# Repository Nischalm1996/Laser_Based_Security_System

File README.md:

# Laser_Based_Security_System

## Pin Connections
| NAME     |PIN|
| ---      | ---|
|LASER|D5|
| LASER1|D6|
| Buzzer|D8|
| LED|D10|
| DETECT|D2|
| DETECT1|D7|
|RX_GSM|D3|
| TX_GSM|D4|

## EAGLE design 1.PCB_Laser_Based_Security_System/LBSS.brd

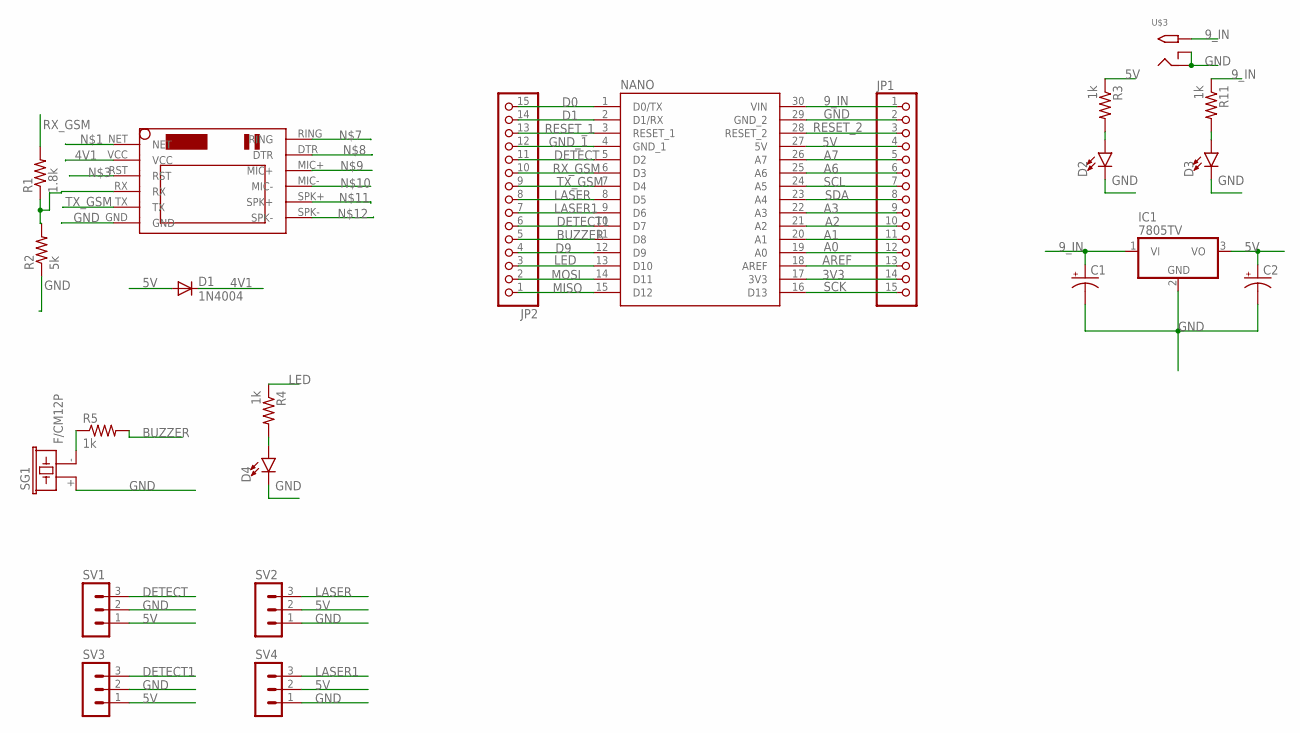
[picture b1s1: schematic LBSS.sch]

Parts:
C1, C2: CPOL-USE3.5-8; E3,5-8
D1: 1N4004; DO41-10
D2, D3, D4: LED3MM; LED_3MM
IC1: 7805TV; TO220V
JP1, JP2: PINHD-1X15; 1X15
NANO: A000005; MODULE_A000005
R1: 1.8k; 0207/10
R2: 5k; 0207/10
R3, R4, R5, R11: 1k; M0805
SG1: F/CM12P
SV1, SV2, SV3, SV4: MA03-1
U$1: SIM800LMODULE
U$3: 2.1MMJACKTHM; PJ-102A

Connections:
3V3: JP1.14, NANO.17 (3V3)
4V1: D1.C, U$1.VCC
5V: C2.+, D1.A, IC1.3 (VO), JP1.4, NANO.27 (5V), R3.1, SV1.1, SV2.2, SV3.1, SV4.2
9_IN: C1.+, IC1.1 (VI), JP1.1, NANO.30 (VIN), R11.1, U$3.TIP
A0: JP1.12, NANO.19 (A0)
A1: JP1.11, NANO.20 (A1)
A2: JP1.10, NANO.21 (A2)
A3: JP1.9, NANO.22 (A3)
A6: JP1.6, NANO.25 (A6)
A7: JP1.5, NANO.26 (A7)
AREF: JP1.13, NANO.18 (AREF)
BUZZER: JP2.5, NANO.11 (D8), R5.2
D0: JP2.15, NANO.1 (D0/TX)
D1: JP2.14, NANO.2 (D1/RX)
D9: JP2.4, NANO.12 (D9)
DETECT: JP2.11, NANO.5 (D2), SV1.3
DETECT1: JP2.6, NANO.10 (D7), SV3.3
GND: C1.-, C2.-, D2.K (C), D3.K (C), D4.K (C), IC1.2 (GND), JP1.2, NANO.29 (GND_2), R2.1, SG1.+ (1), SV1.2, SV2.1, SV3.2, SV4.1, U$1.GND, U$3.RING, U$3.RING_SW
GND_1: JP2.12, NANO.4 (GND_1)
LASER: JP2.8, NANO.8 (D5), SV2.3
LASER1: JP2.7, NANO.9 (D6), SV4.3
LED: JP2.3, NANO.13 (D10), R4.1
MISO: JP2.1, NANO.15 (D12)
MOSI: JP2.2, NANO.14 (D11)
unnamed: D3.A, R11.2
unnamed: R1.1, R2.2, U$1.RX
unnamed: D2.A, R3.2
unnamed: R5.1, SG1.- (2)
unnamed: D4.A, R4.2
RESET_1: JP2.13, NANO.3 (RESET_1)
RESET_2: JP1.3, NANO.28 (RESET_2)
RX_GSM: JP2.10, NANO.6 (D3), R1.2
SCK: JP1.15, NANO.16 (D13)
SCL: JP1.7, NANO.24 (A5)
SDA: JP1.8, NANO.23 (A4)
TX_GSM: JP2.9, NANO.7 (D4), U$1.TX

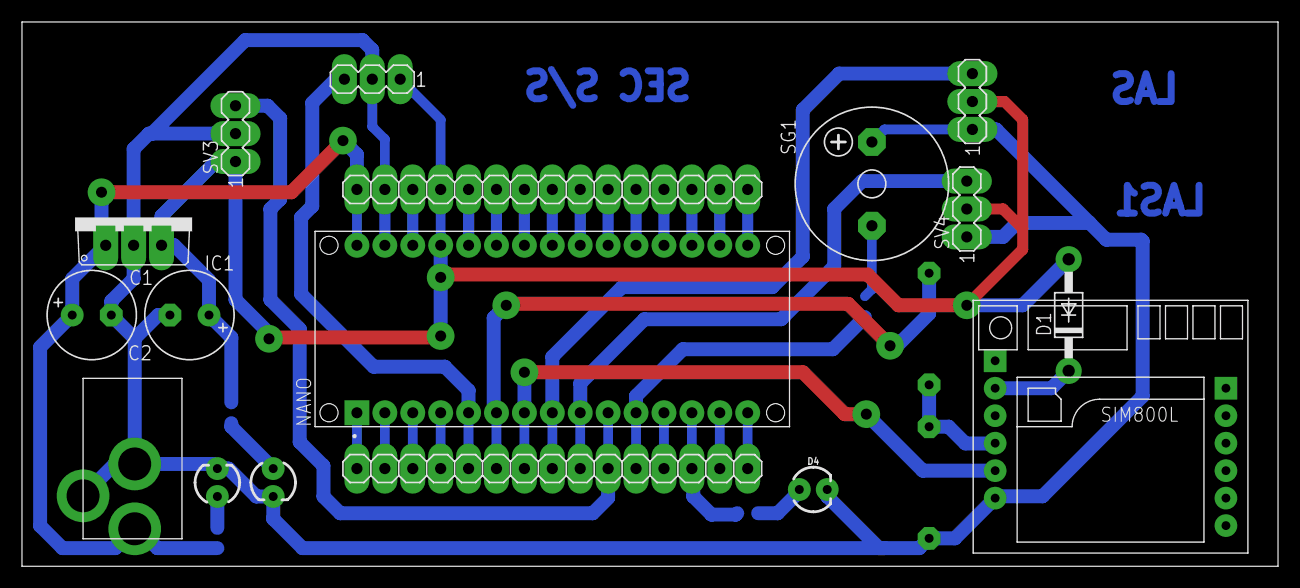
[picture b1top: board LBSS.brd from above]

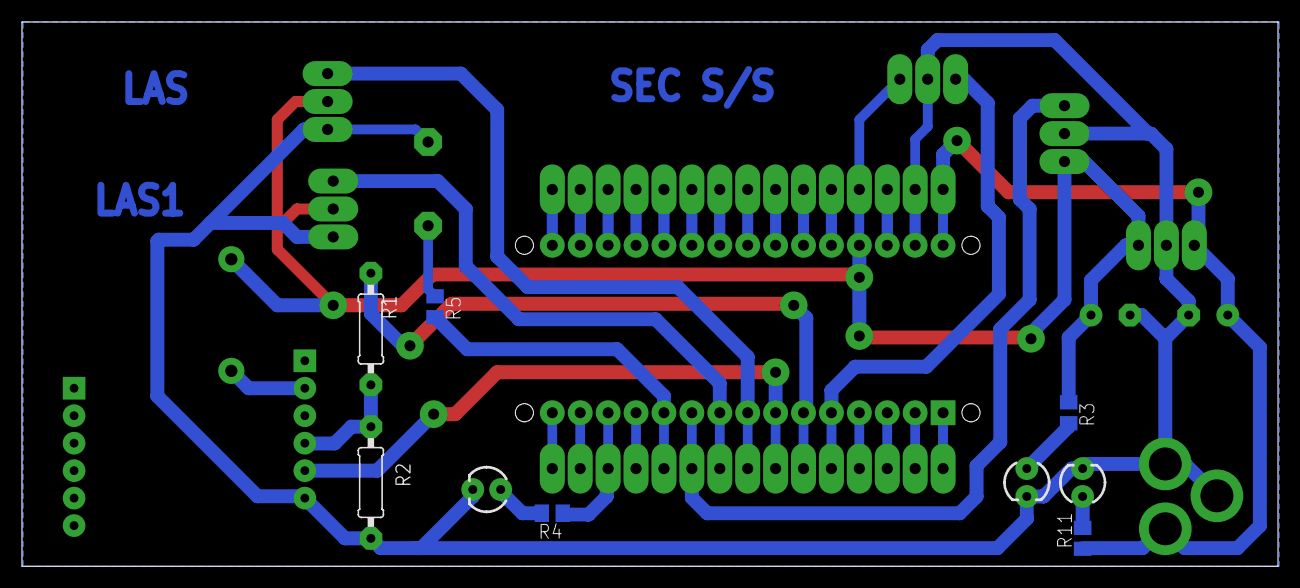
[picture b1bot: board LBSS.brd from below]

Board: 2 copper layers, 114.3 x 49.5 mm, 23 parts (6 on the bottom side), 36 nets.

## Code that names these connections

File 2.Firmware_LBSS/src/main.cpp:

#include <Arduino.h>
#include "Buzzer.h"
#include "LED.h"
#include "LDR.h"
#include "GSM_MODULE.h"
#include "LASER.h"

//7899302011 -- number to send SMS
//SIM CARD number: 7348982783
const String PHONE = "+917899302011";

//Pin definitions to mind
#define BUZZER 8
#define LED 10
#define DETECT 2
#define DETECT1 7
//creating classes
Buzzer buzz(BUZZER);
Led ledObj(LED);
LDR ldrObj(DETECT);
GSM_MODULE gsmObj;
LASER laserobj(LASER_PIN);
int8_t count = 0;

void setup()
{
  pinMode(13, OUTPUT);
  Serial.begin(9600);

  //LED Begin and turn ON and OFF
  ledObj.ledOn();
  delay(2000);
  ledObj.ledOff();
  Serial.println("LEd test Done!");
  //LASER System begin and ON
  laserobj.begin();
  laserobj.laserOn();
  delay(2500);
  laserobj.laserOff();
  Serial.println("Laser test Done!");

  //Buzzer check
  buzz.begin();
  buzz.beep(3000, 5000);
  Serial.println("Buzzer test Done!");
  //LDR begin
  ldrObj.begin();

  //GSM send message

  gsmObj.sendMessage("System initiated! Reply with ON or OFF to control system", PHONE);
  gsmObj.beginReadSMS();
}

void loop()
{

  if (LASER_CONTROL)
  {
    if (ldrObj.readInput())
    {
      ledObj.ledOn();
      buzz.beep(1, 4500);
      count++;
    }
    else
    {
      ledObj.ledOff();
    }
  }

  if (count >= 100)
  {
    Serial.println("INTRUDER!!!");
    //send GSM Message
    buzz.beep(10000, 3000);
    gsmObj.sendMessage("INTRUDER DETECTED!!", PHONE);
    delay(10000);
    count = 0;
  }
  Serial.println(count);
  if (LASER_CONTROL)
  {
    laserobj.laserOn();
    //Serial.println("Laser On");
  }
  else
  {
    laserobj.laserOff();
    //Serial.println("Laser Off");
  }

  gsmObj.readSMSAndAct();
}

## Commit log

2021-03-11 PCB done
    PCB Done
2021-03-11 Added LDR 3d Models
2021-03-12 PCB Done software begining
2021-03-12 initial software commit
2021-03-12 added buzzer.h
2021-03-14 Added Schematic
2021-03-14 File Structure changed
2021-03-14 Added LED.h and testCases
2021-03-14 Added LDR.h
2021-03-14 bug fixes
2021-03-14 added LASER.h
2021-03-14 updated GSM
2021-03-14 random
2021-03-14 added GSM library
2021-03-14 compiled version needs to be tested
2021-03-14 Fixed LED.h needs testing
2021-03-14 added blinking led in setup()
2021-03-16 changed phone
2021-03-28 added GSM send message
2021-03-28 added custom gsm_module.h
2021-03-28 main changes
2021-03-28 Pre_final commit
2021-04-01 Final Commit.
    All system working ready to handoff
2021-04-03 Added Photos and Videos
2021-06-02 number_change
2022-06-07 Added new make files

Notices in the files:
parts and their libraries:
SparkFun-LED: Licensing: Creative Commons ShareAlike 4.0 International - https://creativecommons.org/licenses/by-sa/4.0
